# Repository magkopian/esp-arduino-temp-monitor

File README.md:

Temperature and Humidity Monitor
================================

## Description:

These are the PCB design files and source code for my ESP8266 based temperature and humidity monitor.

The [board](/board) directory contains the KiCAD schematic and PCB layout files together with the [gerber files](/board/gerbers). While the [firmware](/firmware) directory, contains the Arduino source code for the ESP8266. The [server](/server) directory contains the server side script that logs the received data, as well as an SQL file for creating the database tables. Finally, the design files for the enclosure can be found on [Thingiverse](https://www.thingiverse.com/thing:2740731).

For more information and detailed instructions on making your own, checkout my project on [Instructables](https://www.instructables.com/id/Temperature-and-Humidity-Monitor/).

## Programming Instructions:

The firmware can be compiled and burned to an ESP8266 microcontroller using the [Arduino IDE](https://www.arduino.cc/en/Main/Software). To compile the project code you'll also need to install the [SimpleDHT](https://github.com/winlinvip/SimpleDHT/) library package using the [Library Manager](https://www.arduino.cc/en/Guide/Libraries#toc2) of the Arduino IDE. Additionally, for programming the ESP8266 using the Arduino IDE, the [ESP8266 Community](https://github.com/esp8266/Arduino) core package needs to be installed using the [Board Manager](https://www.arduino.cc/en/Guide/Cores).

## License:

The design files for the PCB and the enclosure are all distributed under the [Attribution-ShareAlike 4.0 International](https://creativecommons.org/licenses/by-sa/4.0/) license. The source code for the firmware and the server are distributed under the MIT license.

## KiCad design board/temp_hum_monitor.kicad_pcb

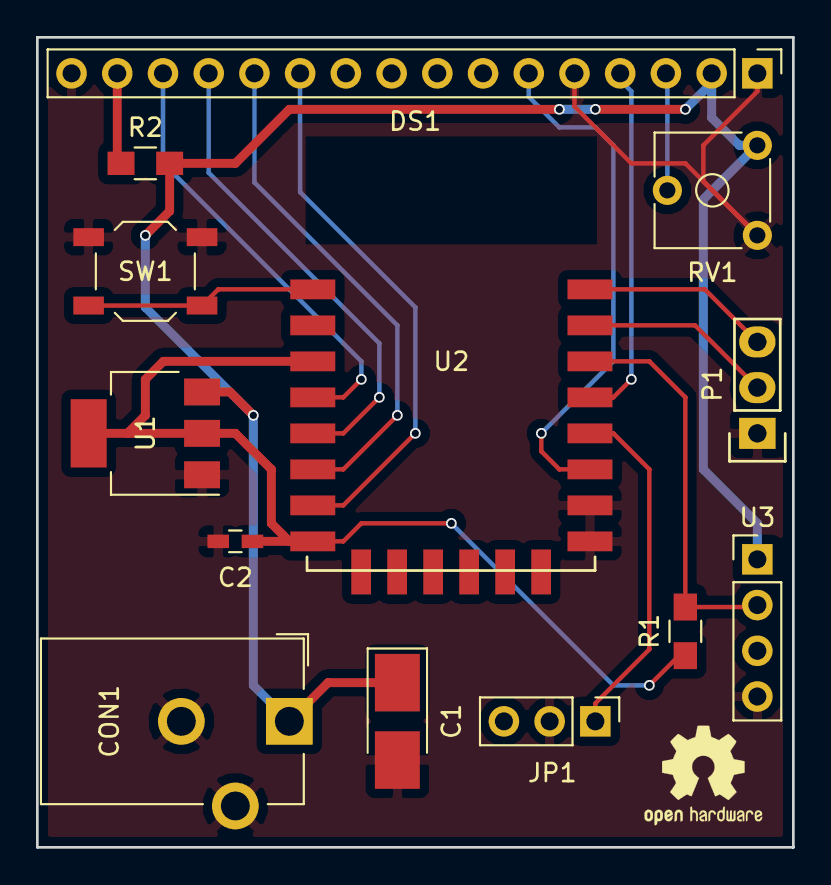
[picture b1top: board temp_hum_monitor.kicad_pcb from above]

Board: 2 copper layers, 42.0 x 45.0 mm, 13 parts (0 on the bottom side), 16 nets.

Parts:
C1: 10uF; CP_Tantalum_Case-B_EIA-3528-21_Hand
C2: 100nF; C_0603_HandSoldering
CON1: POWER_IN; Barrel_Jack_CUI_PJ-102AH
DS1: LCD-016N002L; Pin_Header_Straight_1x16_Pitch2.54mm
JP1: Jumper; Pin_Header_Straight_1x03_Pitch2.54mm
P1: PROGRAMMING_HEADER; Pin_Header_Straight_1x03
R1: 10K; R_0805_HandSoldering
R2: 47R; R_0805_HandSoldering
RV1: 10K; Potentiometer_Trimmer_ACP_CA6v_Horizontal
SW1: RESET; SW_SPST_TL3342
U1: LD1117S33TR; SOT-223-3_TabPin2
U2: ESP-12E; ESP-12E_SMD
U3: DHT11; Pin_Header_Straight_1x04_Pitch2.54mm

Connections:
+3V3: C2.1, R1.1, U1.2, U2.3, U2.8
+5V: C1.1, CON1.1, DS1.2, R2.2, RV1.1, U1.3, U3.1
/ESP_RX: P1.2, U2.15
/ESP_TX: P1.3, U2.16
/LCD_D4: DS1.11, U2.7
/LCD_D5: DS1.12, U2.6
/LCD_D6: DS1.13, U2.5
/LCD_D7: DS1.14, U2.4
/LCD_E: DS1.6, U2.11
/LCD_RS: DS1.4, U2.13
GND: C1.2, C2.2, CON1.2, CON1.3, DS1.1, DS1.5, DS1.16, JP1.2, P1.1, RV1.3, SW1.2, U1.1, U2.9, U2.10, U3.4
unnamed: DS1.3, RV1.2
unnamed: DS1.15, R2.1
unnamed: JP1.1, U2.12
unnamed: R1.2, U2.14, U3.2
unnamed: SW1.1, U2.1

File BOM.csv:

Id,Designator,Package,Quantity,Designation,Supplier and ref
1,U2,ESP-12E_SMD,1,ESP-12E,
2,C1,CP_Tantalum_Case-B_EIA-3528-21_Hand,1,10uF,
3,C2,C_0603_HandSoldering,1,100nF,
4,CON1,Barrel_Jack_CUI_PJ-102AH,1,POWER_IN,
5,DS1,Pin_Header_Straight_1x16_Pitch2.54mm,1,LCD-016N002L,
6,P1,Pin_Header_Straight_1x03,1,PROGRAMMING_HEADER,
7,R1,R_0805_HandSoldering,1,10K,
8,R2,R_0805_HandSoldering,1,47R,
9,RV1,Potentiometer_Trimmer_ACP_CA6v_Horizontal,1,10K,
10,U1,SOT-223-3_TabPin2,1,LD1117S33TR,
11,SW1,SW_SPST_TL3342,1,RESET,
12,JP1,Pin_Header_Straight_1x03_Pitch2.54mm,1,Jumper,
13,U3,Pin_Header_Straight_1x04_Pitch2.54mm,1,DHT11,

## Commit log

2018-01-01 Added PCB design and gerber files
2018-01-01 Added firmware source code
2018-01-01 Added README and LICENSE files
2018-01-01 Added pictures
2018-01-01 Added server side logging script
2018-01-01 Added LICENCE file for server
2018-01-01 Fixed typo
2018-01-04 Added web interface for displaying the data
2018-01-04 Added link to Instructables project
2018-02-13 Fixed undifined index notice with hours with no data
